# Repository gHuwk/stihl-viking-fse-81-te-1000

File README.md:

# stihl-viking-fse-81-te-1000
## About
STIHL stabilizer board for Viking TE-1000, FSE-81
In this repository, as an exercise, we present the reverse of the notorious stabilizer board for the Viking (Stihl) FSE-81 trimmer.

Плата стабилизатора STIHL для Viking TE-1000, FSE-81
В данном репозитории в качесте упражнения представлен реверс небезысвестной платы стабилизатора для тримера Viking (Stihl) FSE-81.
Данный реверс не для коммерческого пользования, является "учебным" проектом для домашнего пользования.
Все претензии направлять в Issue.

## Versions

### Version 0.3 (In-Progress)

TODO: Добавить номиналы резисторов, конденсаторов, обозначить стабилитроны (диоды Зенера) в соответствии с маркировкой, которая стерлась.

TODO: Заменить footprint для ряда компонентов

TODO: Изменить размеры платы + добавить Edge Cuts для производства.

### Version 0.2 (Release)

Изменена схема, добавлено согласование ширины дорожек

### Version 0.1 

Снята схема стабилизатора. Первичный макет.

## Stack

KiCad + Krita

## Pictures

### Reference:

### Scheme:

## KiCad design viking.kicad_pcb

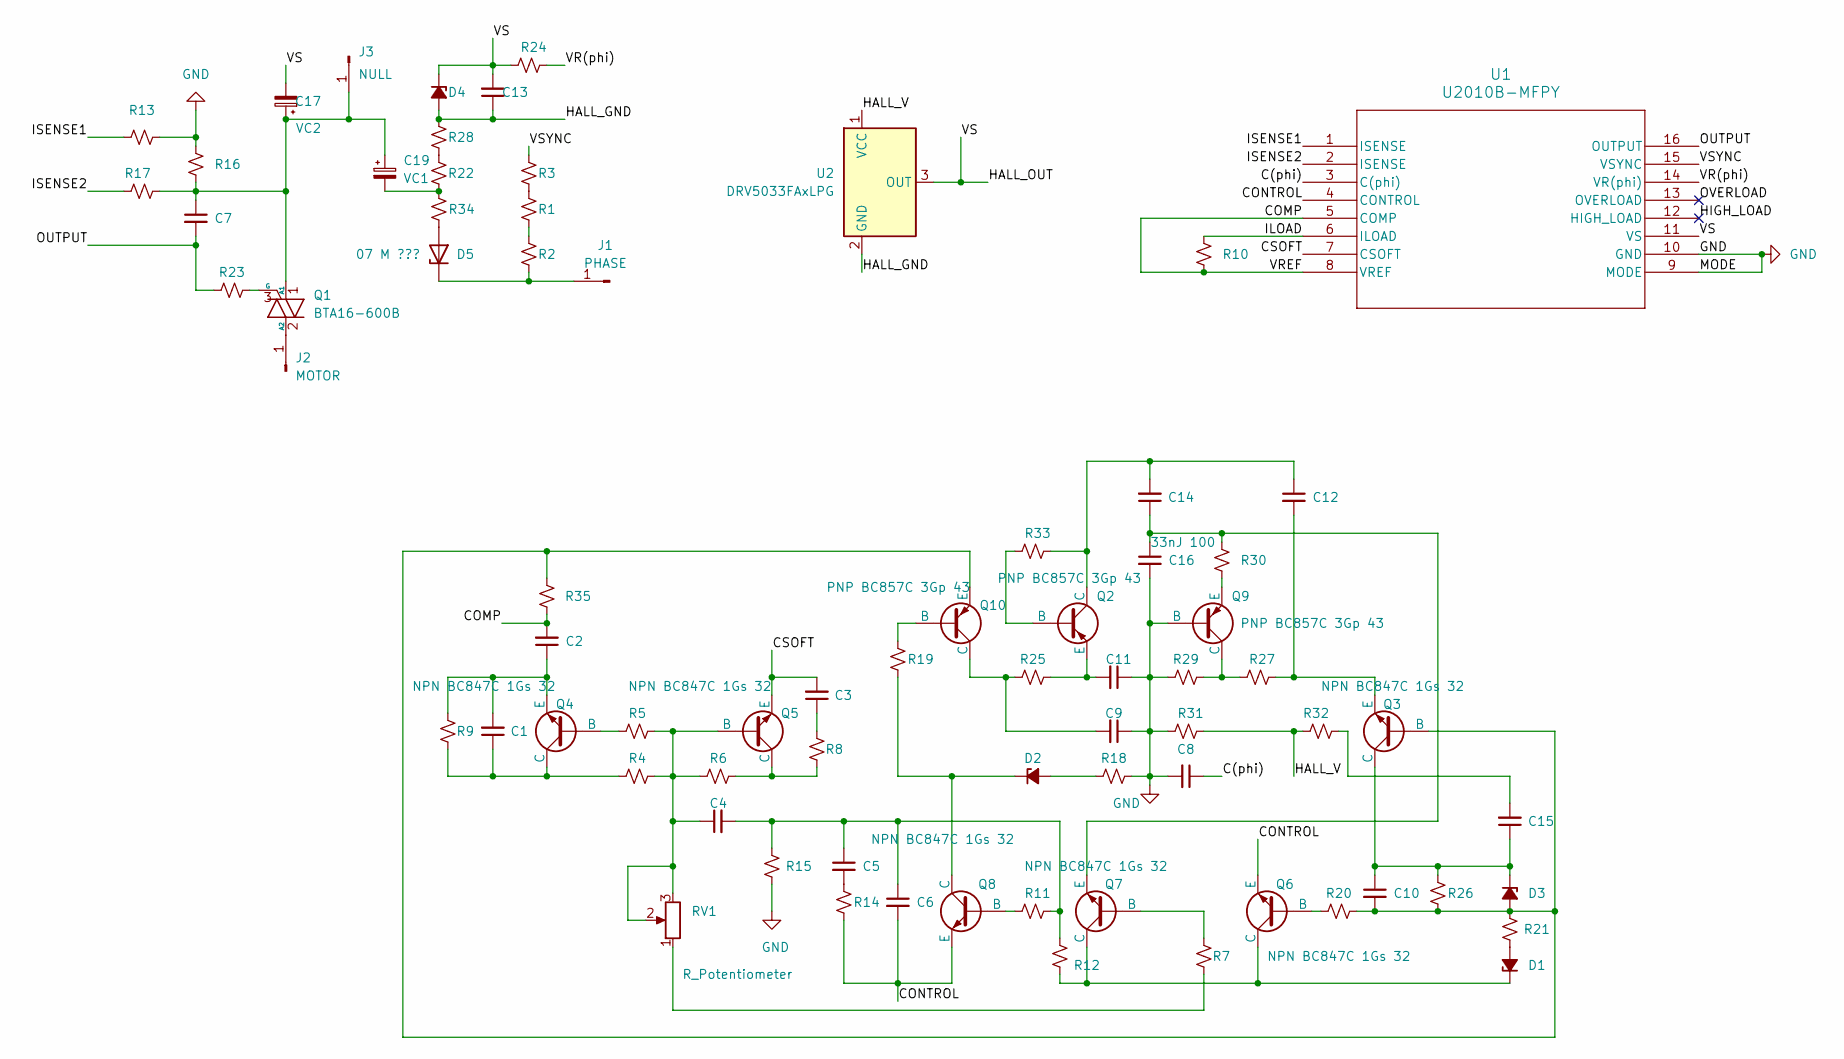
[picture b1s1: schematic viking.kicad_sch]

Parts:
C1, C2, C3, C4, C5, C6, C7, C8, C9, C10, C11, C12, C13, C14, C15: C_Small; C_0805_2012Metric_Pad1.18x1.45mm_HandSolder
C16: 33nJ 100; C_Rect_L7.2mm_W2.5mm_P5.00mm_FKS2_FKP2_MKS2_MKP2
C17: VC2; CP_Radial_D6.3mm_P2.50mm
C19: VC1; CP_Radial_D6.3mm_P2.50mm
D1, D2, D3, D4: D_Zener_Small_Filled; D_1206_3216Metric_Pad1.42x1.75mm_HandSolder
D5: 07 M ???; D_5W_P12.70mm_Horizontal
J1: PHASE; PinSocket_1x01_P2.54mm_Horizontal
J2: MOTOR; PinSocket_1x01_P2.54mm_Horizontal
J3: NULL; PinSocket_1x01_P2.54mm_Horizontal
Q1: BTA16-600B; TO-220-3_Horizontal_TabDown
Q2, Q9, Q10: PNP BC857C 3Gp 43; SOT-23-3
Q3, Q4, Q5, Q6, Q7, Q8: NPN BC847C 1Gs 32; SOT-23-3
R1, R2, R3, R4, R5, R6, R7, R8, R9, R10, R11, R12, R13, R14, R15, R16, R17, R18, R19, R20, R21, R22, R23, R24, R25, R26, R27, R28, R29, R30, R31, R32, R33: R_Small_US; R_0805_2012Metric_Pad1.20x1.40mm_HandSolder
R34: R_Small_US; R_Axial_DIN0414_L11.9mm_D4.5mm_P20.32mm_Horizontal
R35: R_Small_US; R_Axial_Power_L25.0mm_W6.4mm_P27.94mm
RV1: R_Potentiometer; Potentiometer_Bourns_3386F_Vertical
U1: U2010B-MFPY; SO16_MCH
U2: DRV5033FAxLPG; TO-92_Inline

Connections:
/C(phi): C8.1, U1.3 (C(phi))
/COMP: C2.2, R10.2, R35.1, U1.5 (COMP), U1.8 (VREF)
/CONTROL: C6.2, Q6.3 (E), Q8.3 (E), R14.2, U1.4 (CONTROL)
/CSOFT: C3.2, Q5.3 (E), U1.7 (CSOFT)
/HALL_GND: C13.1, D4.2 (A), R28.2, U2.2 (GND)
/HALL_OUT: C13.2, C17.2, D4.1 (K), R24.2, U1.11 (VS), U2.3 (OUT)
/HALL_V: R31.1, R32.1, U2.1 (VCC)
/HIGH_LOAD: U1.12 (HIGH_LOAD)
/ILOAD: R10.1, U1.6 (ILOAD)
/ISENSE1: R13.1, U1.1 (ISENSE)
/ISENSE2: R17.1, U1.2 (ISENSE)
/OUTPUT: C7.2, R23.1, U1.16 (OUTPUT)
/OVERLOAD: U1.13 (OVERLOAD)
/VR(phi): R24.1, U1.14 (VR(phi))
/VSYNC: R3.2, U1.15 (VSYNC)
GND: C8.2, C9.1, C11.1, C16.2, Q9.2 (B), R13.2, R15.2, R16.1, R18.2, R29.1, R31.2, U1.9 (MODE), U1.10 (GND)
unnamed: C3.1, R8.2
unnamed: C4.2, C5.1, C6.1, R11.1, R12.1, R15.1
unnamed: C5.2, R14.1
unnamed: C15.2, R32.2
unnamed: C19.2, R22.1, R34.1
unnamed: D1.2 (A), R21.1
unnamed: D1.1 (K), Q6.1 (C), Q7.1 (C), R12.2
unnamed: D2.2 (A), R18.1
unnamed: D2.1 (K), Q8.1 (C), R19.1
unnamed: C10.2, D3.2 (A), Q3.2 (B), Q10.3 (E), R20.2, R21.2, R26.2, R35.2
unnamed: C10.1, C15.1, D3.1 (K), Q3.1 (C), R26.1
unnamed: D5.2 (A), R34.2
unnamed: D5.1 (K), J1.1, R2.2
unnamed: J2.1, Q1.2 (A2)
unnamed: C7.1, C17.1, C19.1, J3.1, Q1.1 (A1), R16.2, R17.2
unnamed: Q1.3 (G), R23.2
unnamed: Q2.2 (B), R33.2
unnamed: C12.1, C14.2, Q2.1 (C), R33.1
unnamed: C11.2, Q2.3 (E), R25.2
unnamed: C12.2, Q3.3 (E), R27.2
unnamed: Q4.2 (B), R5.2
unnamed: C1.1, Q4.1 (C), R4.2, R9.1
unnamed: C1.2, C2.1, Q4.3 (E), R9.2
unnamed: C4.1, Q5.2 (B), R4.1, R5.1, R6.2, RV1.2, RV1.3
unnamed: Q5.1 (C), R6.1, R8.1
unnamed: Q6.2 (B), R20.1
unnamed: Q7.2 (B), R7.2
unnamed: C14.1, C16.1, Q7.3 (E), R30.2
unnamed: Q8.2 (B), R11.2
unnamed: Q9.1 (C), R27.1, R29.2
unnamed: Q9.3 (E), R30.1
unnamed: Q10.2 (B), R19.2
unnamed: C9.2, Q10.1 (C), R25.1
unnamed: R1.1, R3.1
unnamed: R1.2, R2.1
unnamed: R7.1, RV1.1
unnamed: R22.2, R28.1

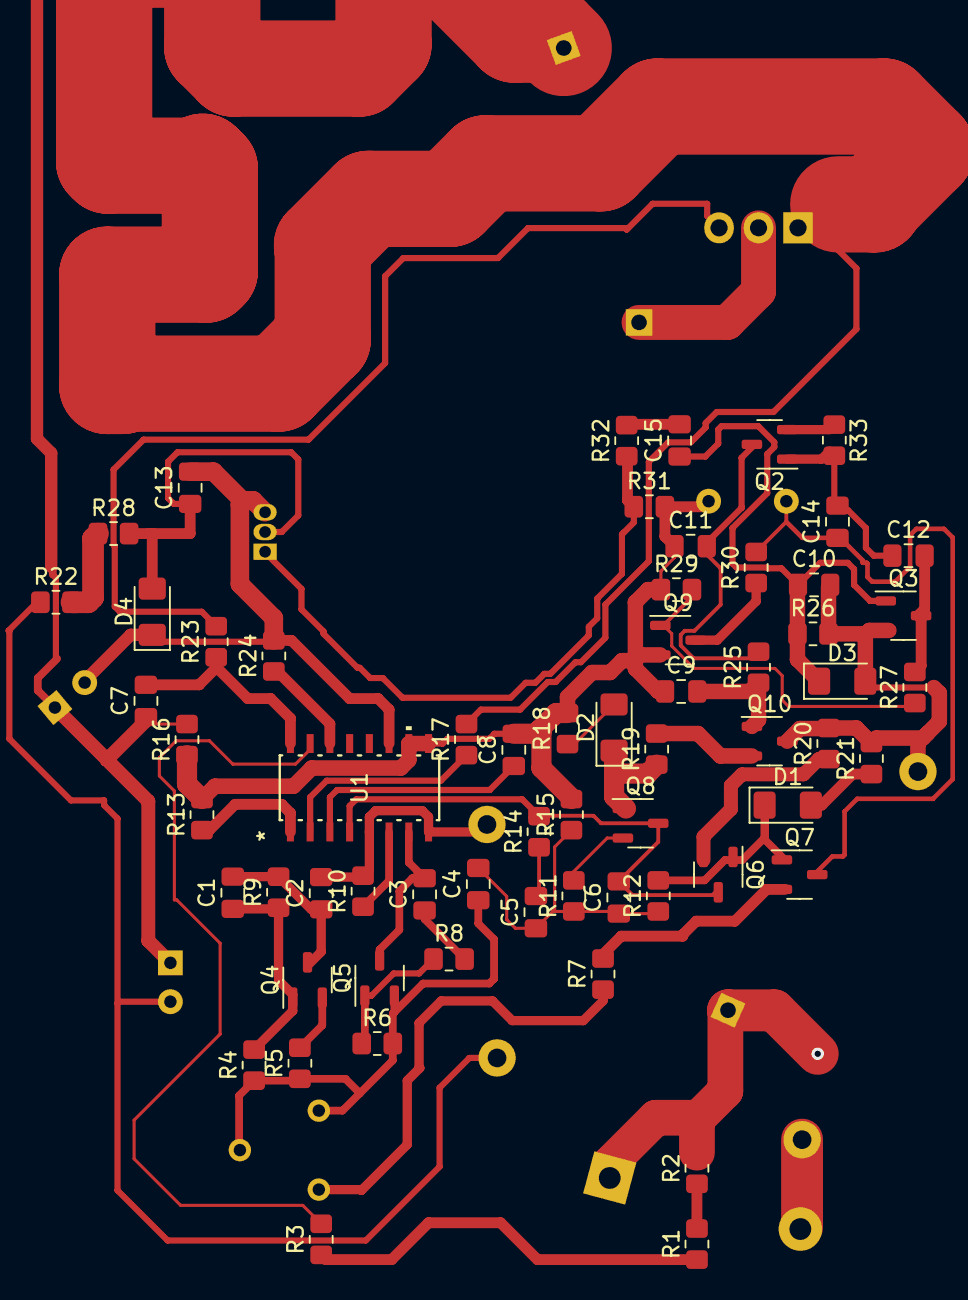
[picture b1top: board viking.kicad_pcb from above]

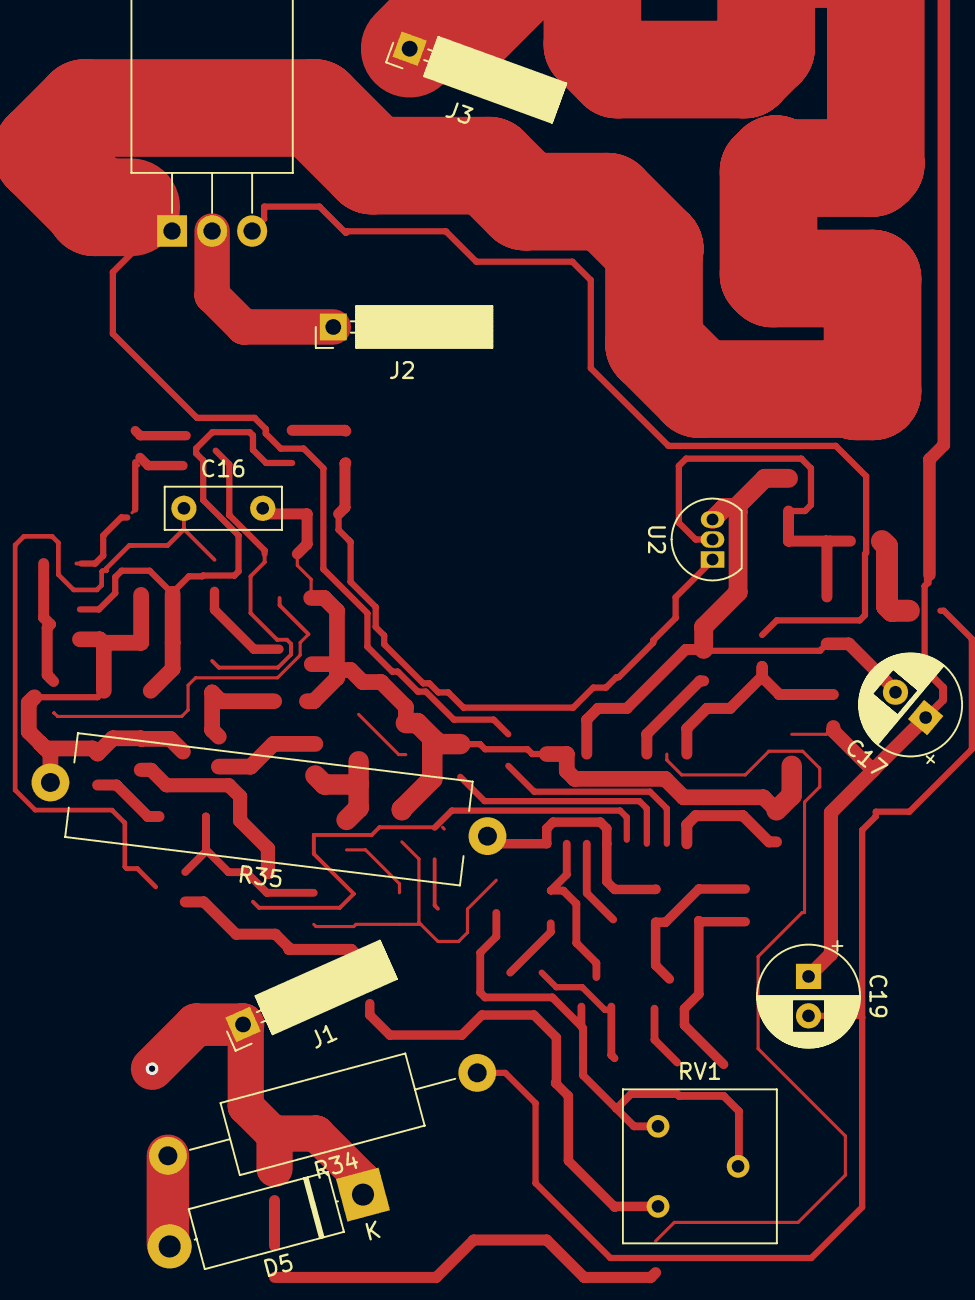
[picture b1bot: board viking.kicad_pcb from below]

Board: 2 copper layers, 74 parts (12 on the bottom side), 51 nets.
